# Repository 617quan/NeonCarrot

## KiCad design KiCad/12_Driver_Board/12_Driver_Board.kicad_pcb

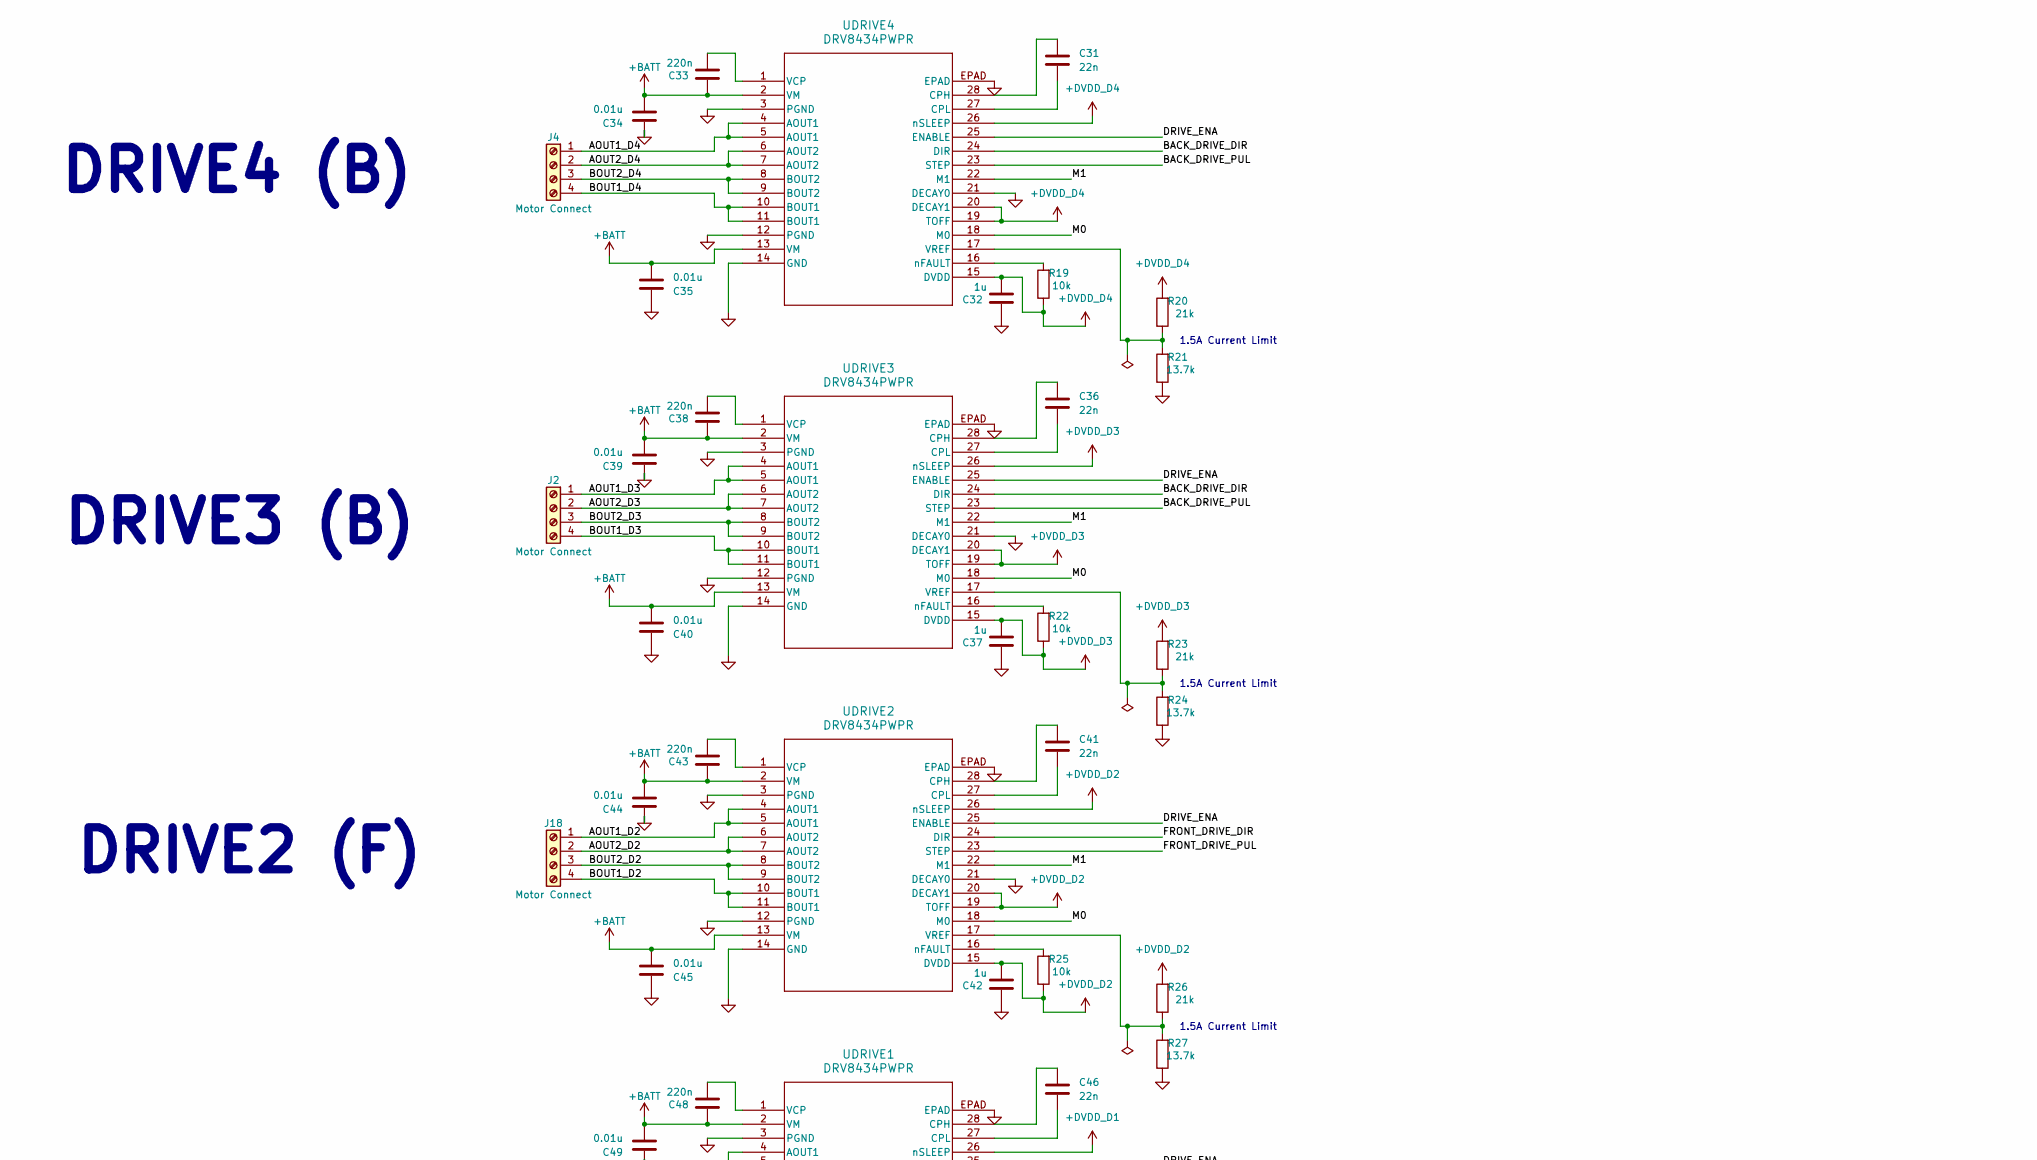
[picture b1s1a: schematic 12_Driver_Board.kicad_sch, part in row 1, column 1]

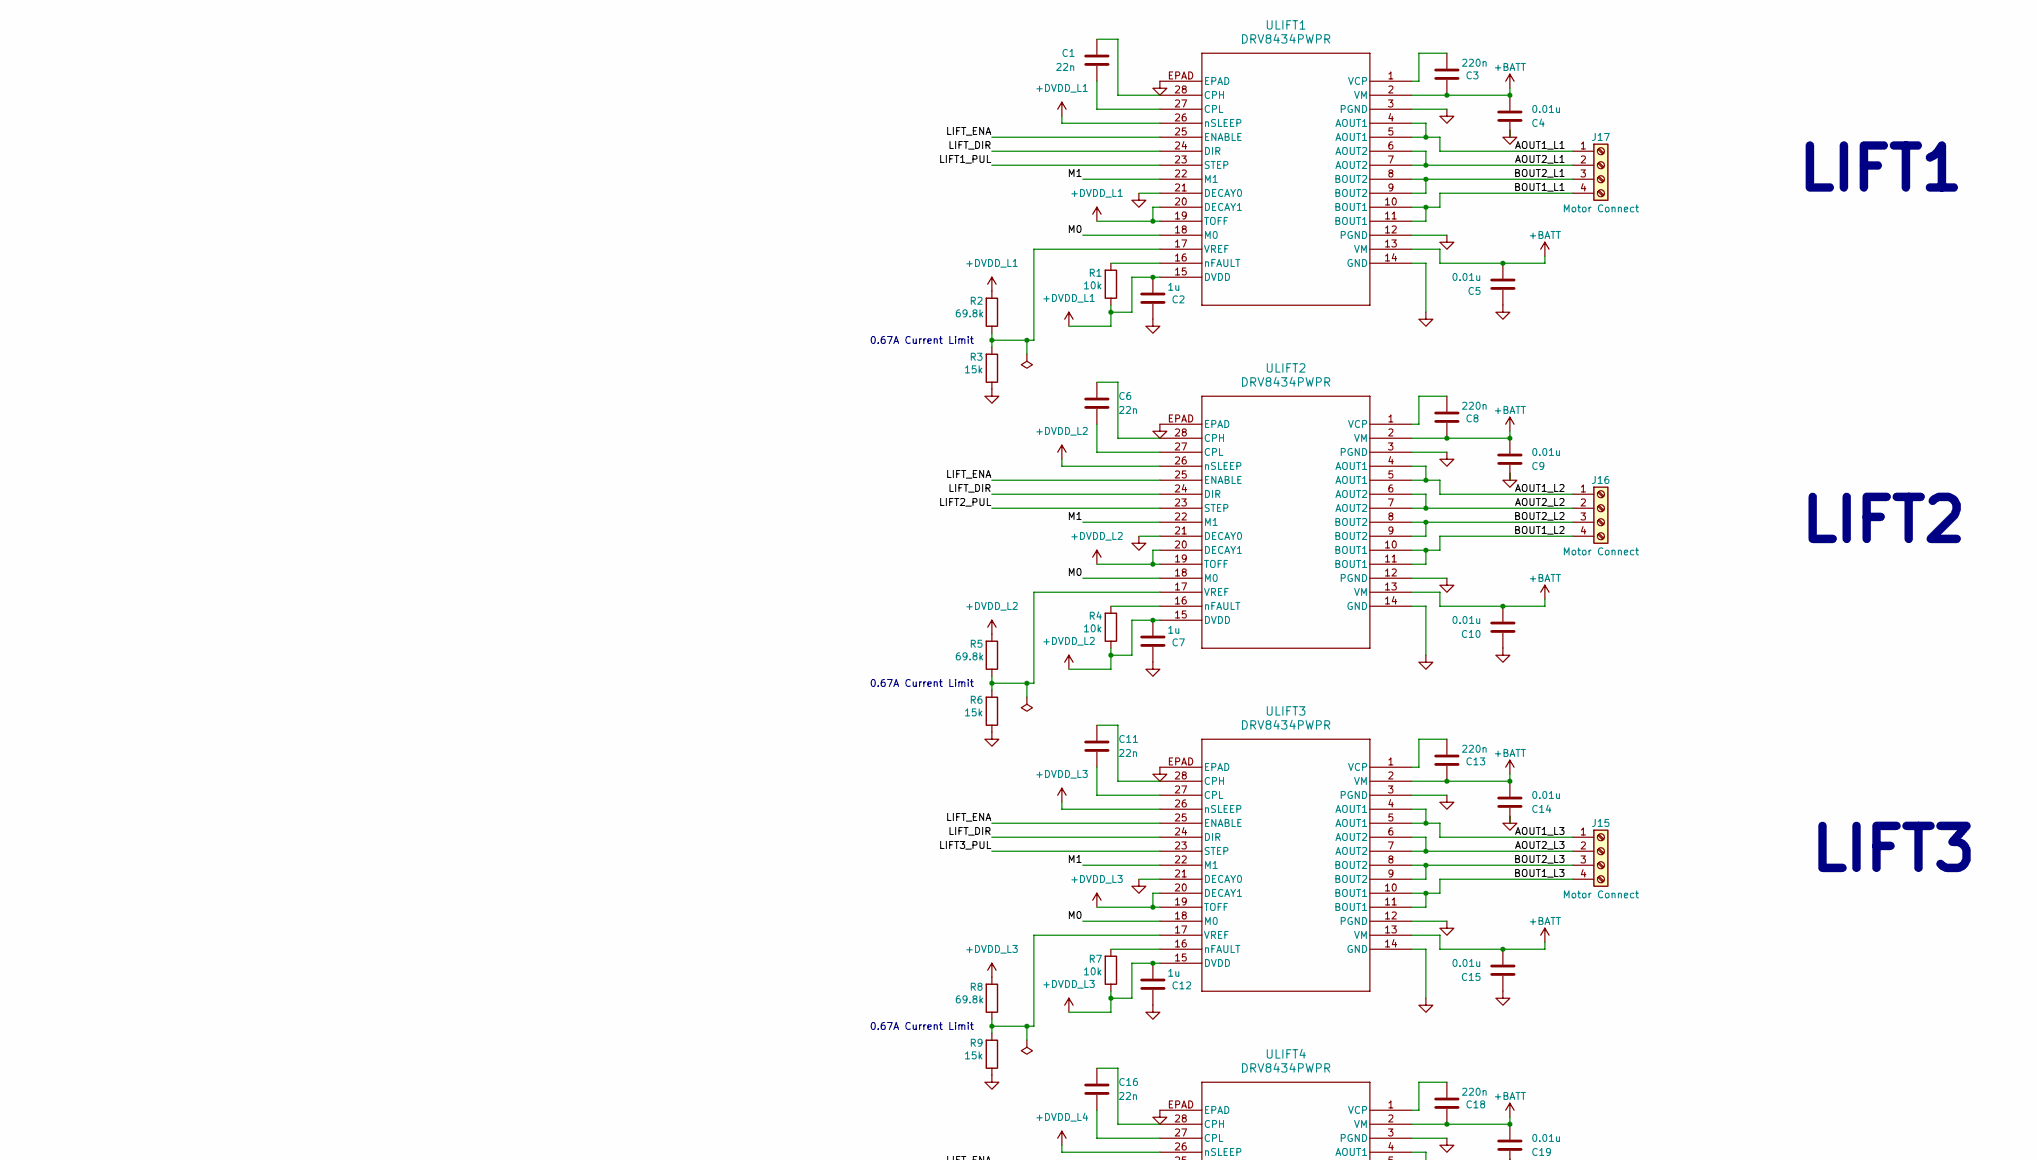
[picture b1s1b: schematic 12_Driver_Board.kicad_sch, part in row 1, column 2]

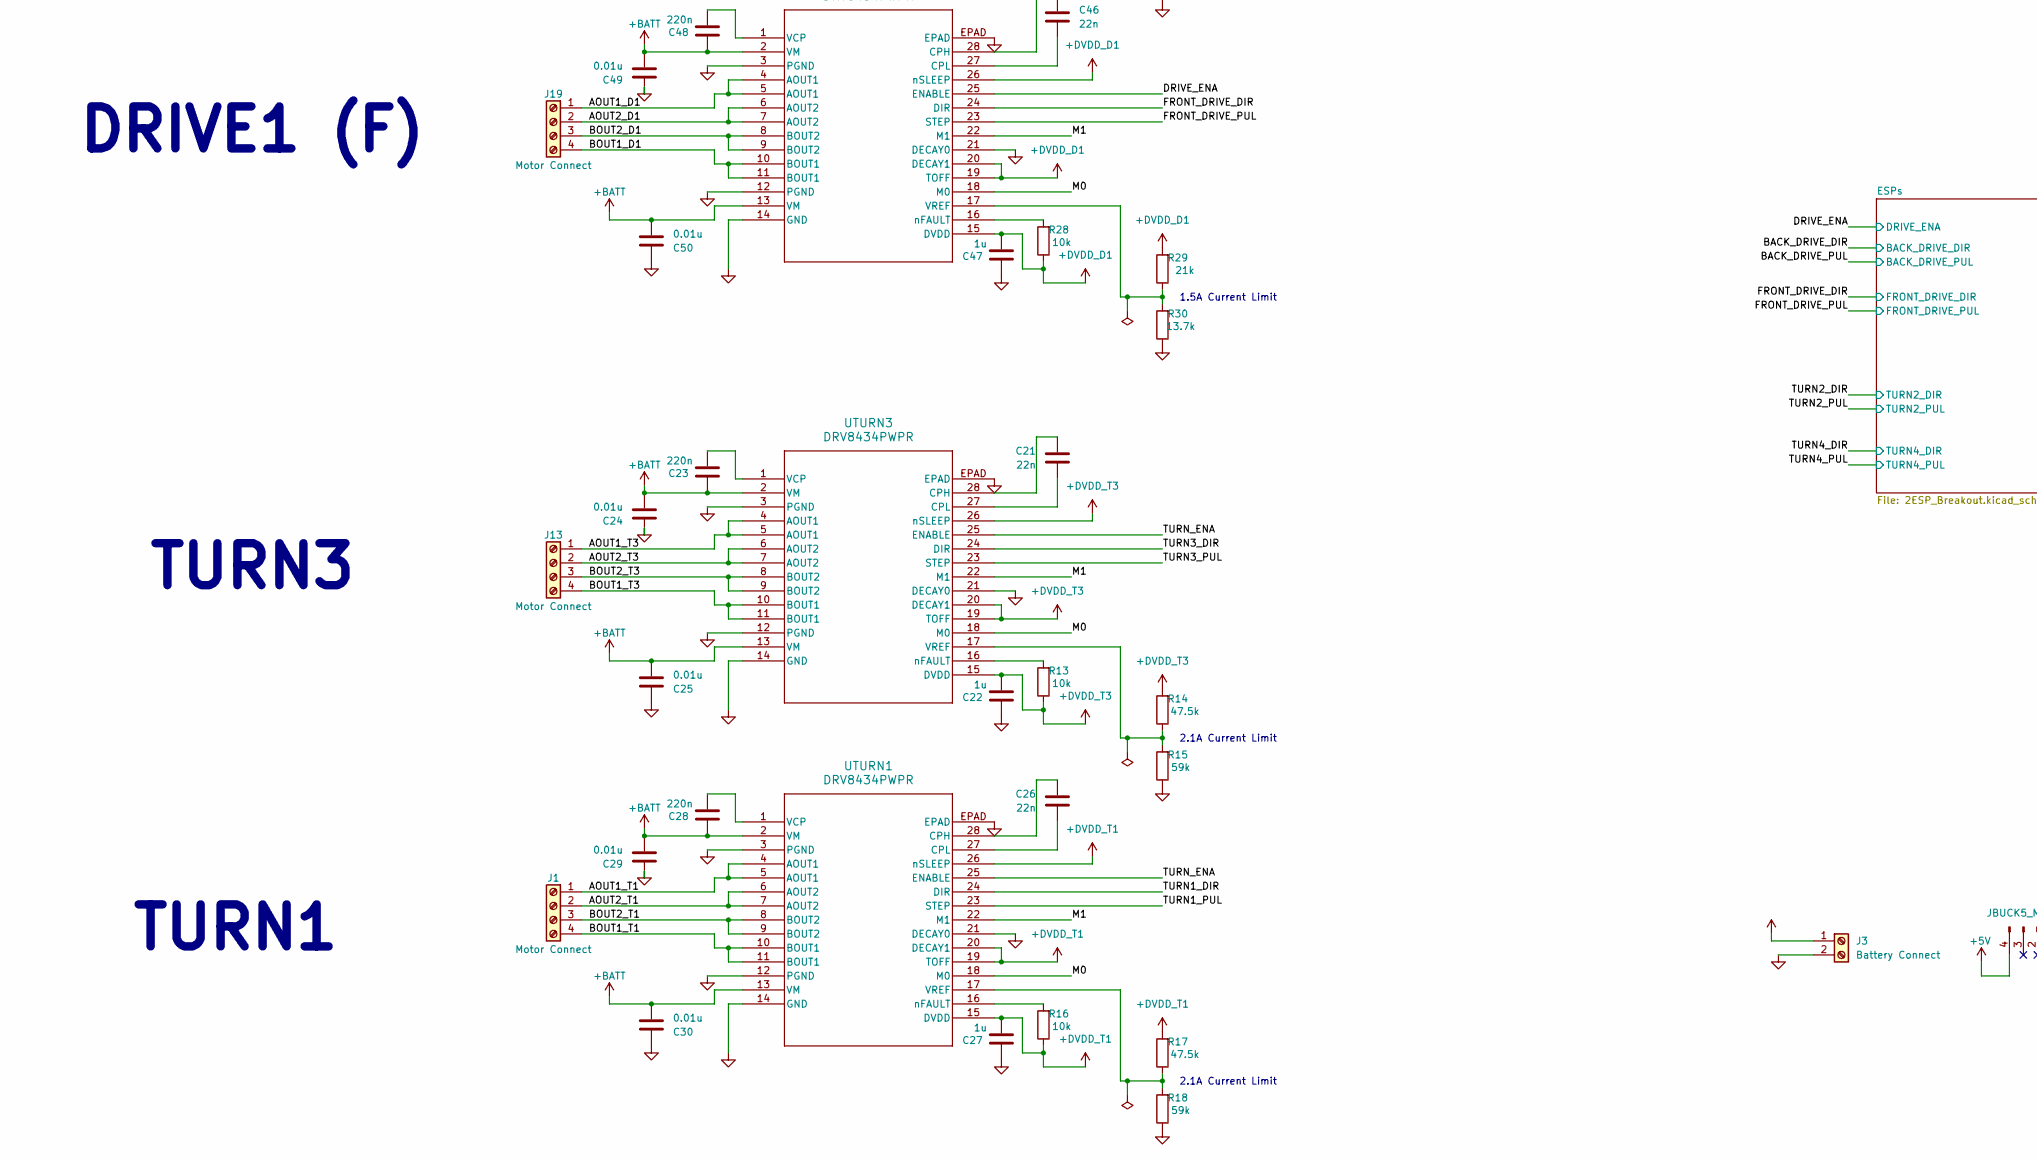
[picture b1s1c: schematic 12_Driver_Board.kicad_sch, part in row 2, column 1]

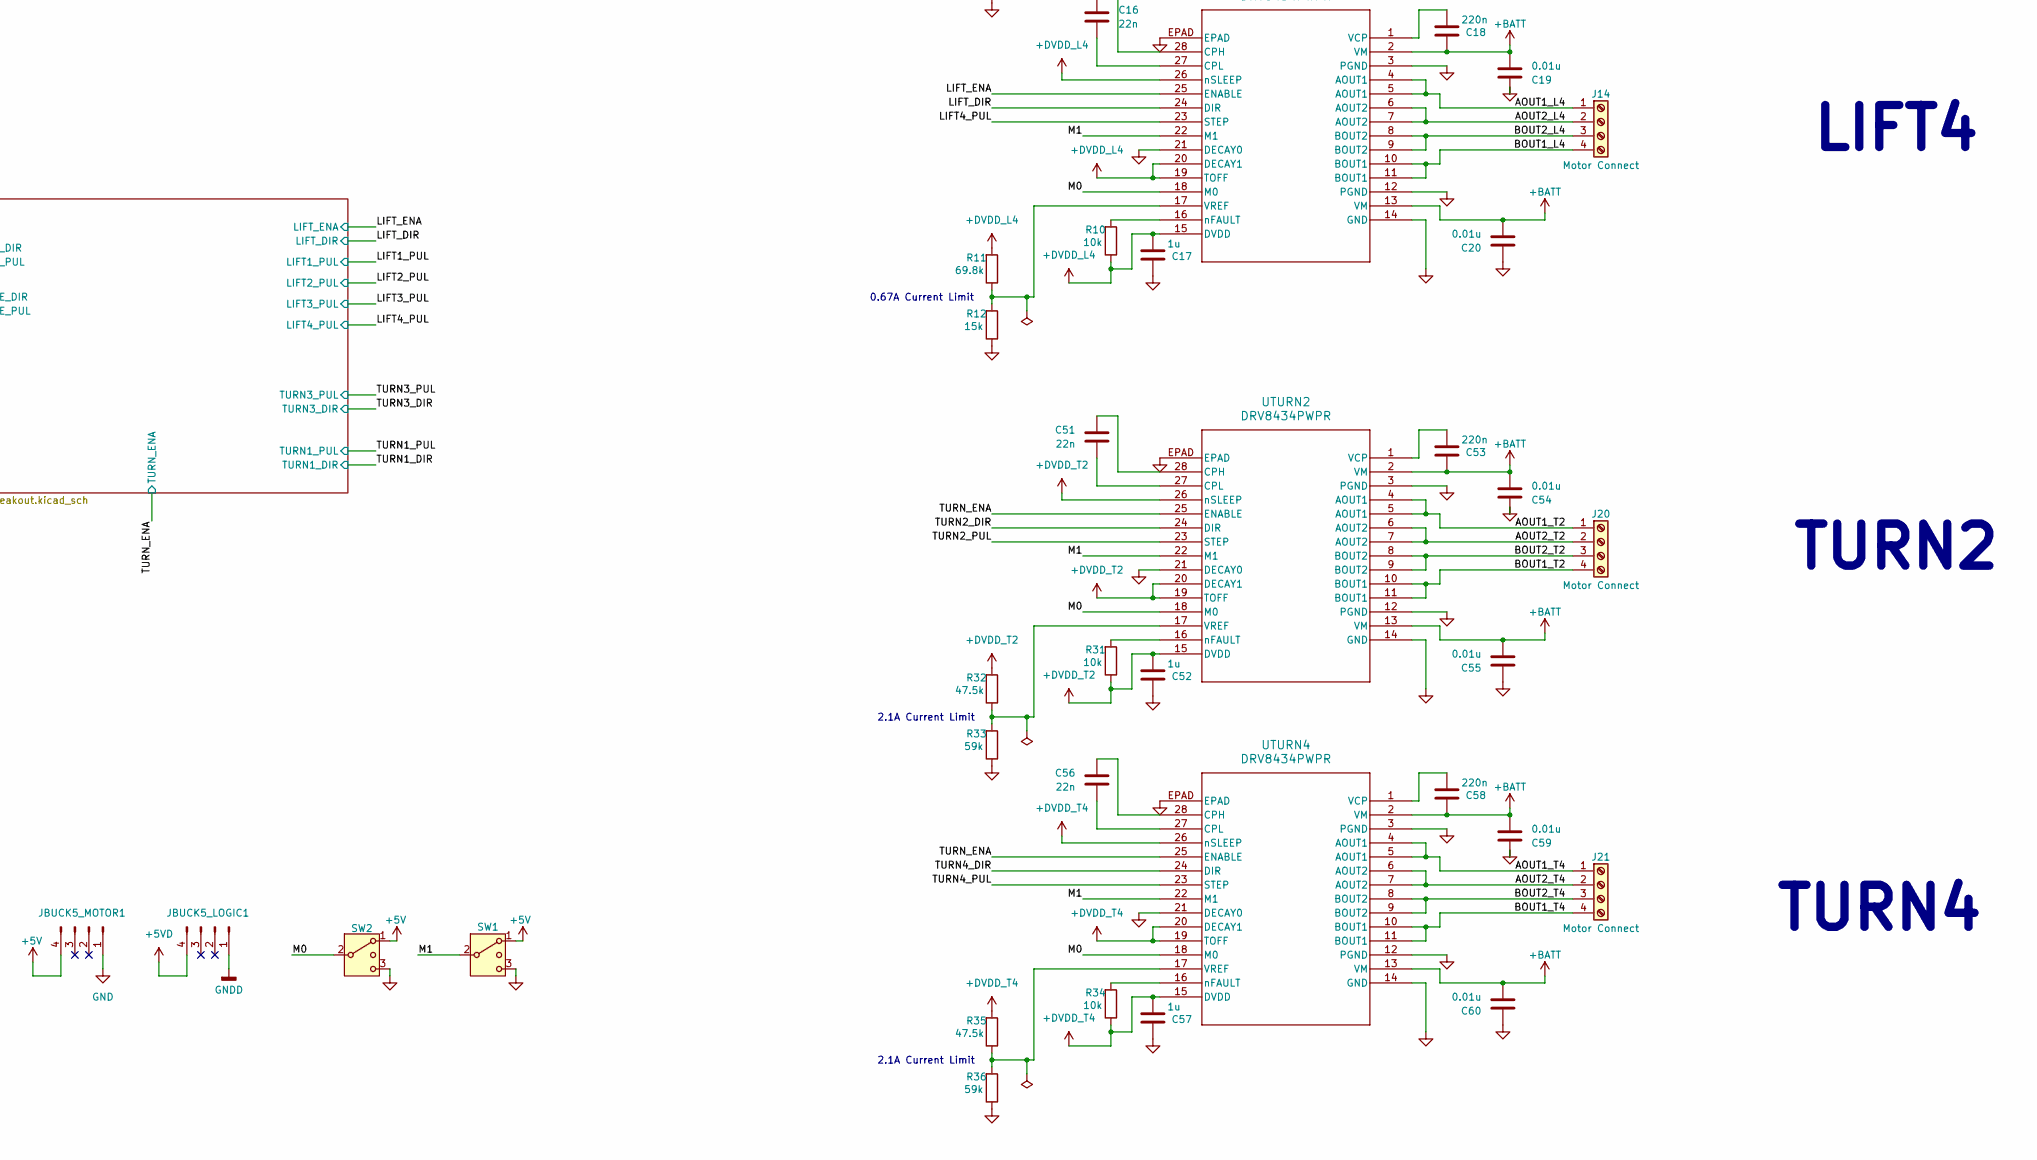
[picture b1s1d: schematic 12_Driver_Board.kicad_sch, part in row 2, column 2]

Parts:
C1, C6, C11, C16, C21, C26, C31, C36, C41, C46, C51, C56: 22n; C_0603_1608Metric
C2, C7, C12, C17, C22, C27, C32, C37, C42, C47, C52, C57: 1u; C_0603_1608Metric
C3, C8, C13, C18, C23, C28, C33, C38, C43, C48, C53, C58: 220n; C_0603_1608Metric
C4, C5, C9, C10, C14, C15, C19, C20, C24, C25, C29, C30, C34, C35, C39, C40, C44, C45, C49, C50, C54, C55, C59, C60: 0.01u; C_0603_1608Metric
J1, J2, J4, J13, J14, J15, J16, J17, J18, J19, J20, J21: Motor Connect; PhoenixContact_MSTBA_2,5_4-G-5,08_1x04_P5.08mm_Horizontal
J3: Battery Connect; PhoenixContact_MSTBA_2,5_2-G-5,08_1x02_P5.08mm_Horizontal
JBUCK5_LOGIC1, JBUCK5_MOTOR1: Conn_01x04_Pin
R1, R4, R7, R10, R13, R16, R19, R22, R25, R28, R31, R34: 10k; R_0603_1608Metric
R2, R5, R8, R11: 69.8k; R_0603_1608Metric
R3, R6, R9, R12: 15k; R_0603_1608Metric
R14, R17, R32, R35: 47.5k; R_0603_1608Metric
R15, R18, R33, R36: 59k; R_0603_1608Metric
R20, R23, R26, R29: 21k; R_0603_1608Metric
R21, R24, R27, R30: 13.7k; R_0603_1608Metric
SW1, SW2: SW_SPDT_MSM; SW_Slide_SPDT_Straight_CK_OS102011MS2Q
UDRIVE1, UDRIVE2, UDRIVE3, UDRIVE4: DRV8434PWPR; TSSOP_34PWPR_TEX
ULIFT1, ULIFT2, ULIFT3, ULIFT4: DRV8434PWPR; TSSOP_34PWPR_TEX
UTURN1, UTURN2, UTURN3, UTURN4: DRV8434PWPR; TSSOP_34PWPR_TEX

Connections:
+5V: JBUCK5_MOTOR1.4, SW1.1, SW2.1; also elsewhere on the board
+BATT: C3.2, C4.1, C5.1, C8.2, C9.1, C10.1, C13.2, C14.1, C15.1, C18.2, C19.1, C20.1, C23.2, C24.1, C25.1, C28.2, C29.1, C30.1, C33.2, C34.1, C35.1, C38.2, C39.1, C40.1, C43.2, C44.1, C45.1, C48.2, C49.1, C50.1, C53.2, C54.1, C55.1, C58.2, C59.1, C60.1, J3.1, UDRIVE1.2 (VM), UDRIVE1.13 (VM), UDRIVE2.2 (VM), UDRIVE2.13 (VM), UDRIVE3.2 (VM), UDRIVE3.13 (VM), UDRIVE4.2 (VM), UDRIVE4.13 (VM), ULIFT1.2 (VM), ULIFT1.13 (VM), ULIFT2.2 (VM), ULIFT2.13 (VM), ULIFT3.2 (VM), ULIFT3.13 (VM), ULIFT4.2 (VM), ULIFT4.13 (VM), UTURN1.2 (VM), UTURN1.13 (VM), UTURN2.2 (VM), UTURN2.13 (VM), UTURN3.2 (VM), UTURN3.13 (VM), UTURN4.2 (VM), UTURN4.13 (VM)
+DVDD_D1: C47.1, R28.1, R29.2, UDRIVE1.15 (DVDD), UDRIVE1.19 (TOFF), UDRIVE1.20 (DECAY1), UDRIVE1.26 (nSLEEP)
+DVDD_D2: C42.1, R25.1, R26.2, UDRIVE2.15 (DVDD), UDRIVE2.19 (TOFF), UDRIVE2.20 (DECAY1), UDRIVE2.26 (nSLEEP)
+DVDD_D3: C37.1, R22.1, R23.2, UDRIVE3.15 (DVDD), UDRIVE3.19 (TOFF), UDRIVE3.20 (DECAY1), UDRIVE3.26 (nSLEEP)
+DVDD_D4: C32.1, R19.1, R20.2, UDRIVE4.15 (DVDD), UDRIVE4.19 (TOFF), UDRIVE4.20 (DECAY1), UDRIVE4.26 (nSLEEP)
+DVDD_L1: C2.1, R1.1, R2.2, ULIFT1.15 (DVDD), ULIFT1.19 (TOFF), ULIFT1.20 (DECAY1), ULIFT1.26 (nSLEEP)
+DVDD_L2: C7.1, R4.1, R5.2, ULIFT2.15 (DVDD), ULIFT2.19 (TOFF), ULIFT2.20 (DECAY1), ULIFT2.26 (nSLEEP)
+DVDD_L3: C12.1, R7.1, R8.2, ULIFT3.15 (DVDD), ULIFT3.19 (TOFF), ULIFT3.20 (DECAY1), ULIFT3.26 (nSLEEP)
+DVDD_L4: C17.1, R10.1, R11.2, ULIFT4.15 (DVDD), ULIFT4.19 (TOFF), ULIFT4.20 (DECAY1), ULIFT4.26 (nSLEEP)
+DVDD_T1: C27.1, R16.1, R17.2, UTURN1.15 (DVDD), UTURN1.19 (TOFF), UTURN1.20 (DECAY1), UTURN1.26 (nSLEEP)
+DVDD_T2: C52.1, R31.1, R32.2, UTURN2.15 (DVDD), UTURN2.19 (TOFF), UTURN2.20 (DECAY1), UTURN2.26 (nSLEEP)
+DVDD_T3: C22.1, R13.1, R14.2, UTURN3.15 (DVDD), UTURN3.19 (TOFF), UTURN3.20 (DECAY1), UTURN3.26 (nSLEEP)
+DVDD_T4: C57.1, R34.1, R35.2, UTURN4.15 (DVDD), UTURN4.19 (TOFF), UTURN4.20 (DECAY1), UTURN4.26 (nSLEEP)
/AOUT1_D1: J19.1, UDRIVE1.4 (AOUT1), UDRIVE1.5 (AOUT1)
/AOUT1_D2: J18.1, UDRIVE2.4 (AOUT1), UDRIVE2.5 (AOUT1)
/AOUT1_D3: J2.1, UDRIVE3.4 (AOUT1), UDRIVE3.5 (AOUT1)
/AOUT1_D4: J4.1, UDRIVE4.4 (AOUT1), UDRIVE4.5 (AOUT1)
/AOUT1_L1: J17.1, ULIFT1.4 (AOUT1), ULIFT1.5 (AOUT1)
/AOUT1_L2: J16.1, ULIFT2.4 (AOUT1), ULIFT2.5 (AOUT1)
/AOUT1_L3: J15.1, ULIFT3.4 (AOUT1), ULIFT3.5 (AOUT1)
/AOUT1_L4: J14.1, ULIFT4.4 (AOUT1), ULIFT4.5 (AOUT1)
/AOUT1_T1: J1.1, UTURN1.4 (AOUT1), UTURN1.5 (AOUT1)
/AOUT1_T2: J20.1, UTURN2.4 (AOUT1), UTURN2.5 (AOUT1)
/AOUT1_T3: J13.1, UTURN3.4 (AOUT1), UTURN3.5 (AOUT1)
/AOUT1_T4: J21.1, UTURN4.4 (AOUT1), UTURN4.5 (AOUT1)
/AOUT2_D1: J19.2, UDRIVE1.6 (AOUT2), UDRIVE1.7 (AOUT2)
/AOUT2_D2: J18.2, UDRIVE2.6 (AOUT2), UDRIVE2.7 (AOUT2)
/AOUT2_D3: J2.2, UDRIVE3.6 (AOUT2), UDRIVE3.7 (AOUT2)
/AOUT2_D4: J4.2, UDRIVE4.6 (AOUT2), UDRIVE4.7 (AOUT2)
/AOUT2_L1: J17.2, ULIFT1.6 (AOUT2), ULIFT1.7 (AOUT2)
/AOUT2_L2: J16.2, ULIFT2.6 (AOUT2), ULIFT2.7 (AOUT2)
/AOUT2_L3: J15.2, ULIFT3.6 (AOUT2), ULIFT3.7 (AOUT2)
/AOUT2_L4: J14.2, ULIFT4.6 (AOUT2), ULIFT4.7 (AOUT2)
/AOUT2_T1: J1.2, UTURN1.6 (AOUT2), UTURN1.7 (AOUT2)
/AOUT2_T2: J20.2, UTURN2.6 (AOUT2), UTURN2.7 (AOUT2)
/AOUT2_T3: J13.2, UTURN3.6 (AOUT2), UTURN3.7 (AOUT2)
/AOUT2_T4: J21.2, UTURN4.6 (AOUT2), UTURN4.7 (AOUT2)
/BACK_DRIVE_DIR: UDRIVE3.24 (DIR), UDRIVE4.24 (DIR); also elsewhere on the board
/BACK_DRIVE_PUL: UDRIVE3.23 (STEP), UDRIVE4.23 (STEP); also elsewhere on the board
/BOUT1_D1: J19.4, UDRIVE1.10 (BOUT1), UDRIVE1.11 (BOUT1)
/BOUT1_D2: J18.4, UDRIVE2.10 (BOUT1), UDRIVE2.11 (BOUT1)
/BOUT1_D3: J2.4, UDRIVE3.10 (BOUT1), UDRIVE3.11 (BOUT1)
/BOUT1_D4: J4.4, UDRIVE4.10 (BOUT1), UDRIVE4.11 (BOUT1)
/BOUT1_L1: J17.4, ULIFT1.10 (BOUT1), ULIFT1.11 (BOUT1)
/BOUT1_L2: J16.4, ULIFT2.10 (BOUT1), ULIFT2.11 (BOUT1)
/BOUT1_L3: J15.4, ULIFT3.10 (BOUT1), ULIFT3.11 (BOUT1)
/BOUT1_L4: J14.4, ULIFT4.10 (BOUT1), ULIFT4.11 (BOUT1)
/BOUT1_T1: J1.4, UTURN1.10 (BOUT1), UTURN1.11 (BOUT1)
/BOUT1_T2: J20.4, UTURN2.10 (BOUT1), UTURN2.11 (BOUT1)
/BOUT1_T3: J13.4, UTURN3.10 (BOUT1), UTURN3.11 (BOUT1)
/BOUT1_T4: J21.4, UTURN4.10 (BOUT1), UTURN4.11 (BOUT1)
/BOUT2_D1: J19.3, UDRIVE1.8 (BOUT2), UDRIVE1.9 (BOUT2)
/BOUT2_D2: J18.3, UDRIVE2.8 (BOUT2), UDRIVE2.9 (BOUT2)
/BOUT2_D3: J2.3, UDRIVE3.8 (BOUT2), UDRIVE3.9 (BOUT2)
/BOUT2_D4: J4.3, UDRIVE4.8 (BOUT2), UDRIVE4.9 (BOUT2)
/BOUT2_L1: J17.3, ULIFT1.8 (BOUT2), ULIFT1.9 (BOUT2)
/BOUT2_L2: J16.3, ULIFT2.8 (BOUT2), ULIFT2.9 (BOUT2)
/BOUT2_L3: J15.3, ULIFT3.8 (BOUT2), ULIFT3.9 (BOUT2)
/BOUT2_L4: J14.3, ULIFT4.8 (BOUT2), ULIFT4.9 (BOUT2)
/BOUT2_T1: J1.3, UTURN1.8 (BOUT2), UTURN1.9 (BOUT2)
/BOUT2_T2: J20.3, UTURN2.8 (BOUT2), UTURN2.9 (BOUT2)
/BOUT2_T3: J13.3, UTURN3.8 (BOUT2), UTURN3.9 (BOUT2)
/BOUT2_T4: J21.3, UTURN4.8 (BOUT2), UTURN4.9 (BOUT2)
/DRIVE_ENA: UDRIVE1.25 (ENABLE), UDRIVE2.25 (ENABLE), UDRIVE3.25 (ENABLE), UDRIVE4.25 (ENABLE); also elsewhere on the board
/FRONT_DRIVE_DIR: UDRIVE1.24 (DIR), UDRIVE2.24 (DIR); also elsewhere on the board
/FRONT_DRIVE_PUL: UDRIVE1.23 (STEP), UDRIVE2.23 (STEP); also elsewhere on the board
/LIFT1_PUL: ULIFT1.23 (STEP); also elsewhere on the board
/LIFT2_PUL: ULIFT2.23 (STEP); also elsewhere on the board
/LIFT3_PUL: ULIFT3.23 (STEP); also elsewhere on the board
/LIFT4_PUL: ULIFT4.23 (STEP); also elsewhere on the board
/LIFT_DIR: ULIFT1.24 (DIR), ULIFT2.24 (DIR), ULIFT3.24 (DIR), ULIFT4.24 (DIR); also elsewhere on the board
/LIFT_ENA: ULIFT1.25 (ENABLE), ULIFT2.25 (ENABLE), ULIFT3.25 (ENABLE), ULIFT4.25 (ENABLE); also elsewhere on the board
/M0: SW2.2 (3), UDRIVE1.18 (M0), UDRIVE2.18 (M0), UDRIVE3.18 (M0), UDRIVE4.18 (M0), ULIFT1.18 (M0), ULIFT2.18 (M0), ULIFT3.18 (M0), ULIFT4.18 (M0), UTURN1.18 (M0), UTURN2.18 (M0), UTURN3.18 (M0), UTURN4.18 (M0)
/M1: SW1.2 (3), UDRIVE1.22 (M1), UDRIVE2.22 (M1), UDRIVE3.22 (M1), UDRIVE4.22 (M1), ULIFT1.22 (M1), ULIFT2.22 (M1), ULIFT3.22 (M1), ULIFT4.22 (M1), UTURN1.22 (M1), UTURN2.22 (M1), UTURN3.22 (M1), UTURN4.22 (M1)
/TURN1_DIR: UTURN1.24 (DIR); also elsewhere on the board
/TURN1_PUL: UTURN1.23 (STEP); also elsewhere on the board
/TURN2_DIR: UTURN2.24 (DIR); also elsewhere on the board
/TURN2_PUL: UTURN2.23 (STEP); also elsewhere on the board
/TURN3_DIR: UTURN3.24 (DIR); also elsewhere on the board
/TURN3_PUL: UTURN3.23 (STEP); also elsewhere on the board
/TURN4_DIR: UTURN4.24 (DIR); also elsewhere on the board
/TURN4_PUL: UTURN4.23 (STEP); also elsewhere on the board
/TURN_ENA: UTURN1.25 (ENABLE), UTURN2.25 (ENABLE), UTURN3.25 (ENABLE), UTURN4.25 (ENABLE); also elsewhere on the board
GND: C2.2, C4.2, C5.2, C7.2, C9.2, C10.2, C12.2, C14.2, C15.2, C17.2, C19.2, C20.2, C22.2, C24.2, C25.2, C27.2, C29.2, C30.2, C32.2, C34.2, C35.2, C37.2, C39.2, C40.2, C42.2, C44.2, C45.2, C47.2, C49.2, C50.2, C52.2, C54.2, C55.2, C57.2, C59.2, C60.2, J3.2, JBUCK5_MOTOR1.1, R3.1, R6.1, R9.1, R12.1, R15.1, R18.1, R21.1, R24.1, R27.1, R30.1, R33.1, R36.1, SW1.3 (4), SW2.3 (4), UDRIVE1.3 (PGND), UDRIVE1.12 (PGND), UDRIVE1.14 (GND), UDRIVE1.21 (DECAY0), UDRIVE1.EPAD, UDRIVE2.3 (PGND), UDRIVE2.12 (PGND), UDRIVE2.14 (GND), UDRIVE2.21 (DECAY0), UDRIVE2.EPAD, UDRIVE3.3 (PGND), UDRIVE3.12 (PGND), UDRIVE3.14 (GND), UDRIVE3.21 (DECAY0), UDRIVE3.EPAD, UDRIVE4.3 (PGND), UDRIVE4.12 (PGND), UDRIVE4.14 (GND), UDRIVE4.21 (DECAY0), UDRIVE4.EPAD, ULIFT1.3 (PGND), ULIFT1.12 (PGND), ULIFT1.14 (GND), ULIFT1.21 (DECAY0), ULIFT1.EPAD, ULIFT2.3 (PGND), ULIFT2.12 (PGND), ULIFT2.14 (GND), ULIFT2.21 (DECAY0), ULIFT2.EPAD, ULIFT3.3 (PGND), ULIFT3.12 (PGND), ULIFT3.14 (GND), ULIFT3.21 (DECAY0), ULIFT3.EPAD, ULIFT4.3 (PGND), ULIFT4.12 (PGND), ULIFT4.14 (GND), ULIFT4.21 (DECAY0), ULIFT4.EPAD, UTURN1.3 (PGND), UTURN1.12 (PGND), UTURN1.14 (GND), UTURN1.21 (DECAY0), UTURN1.EPAD, UTURN2.3 (PGND), UTURN2.12 (PGND), UTURN2.14 (GND), UTURN2.21 (DECAY0), UTURN2.EPAD, UTURN3.3 (PGND), UTURN3.12 (PGND), UTURN3.14 (GND), UTURN3.21 (DECAY0), UTURN3.EPAD, UTURN4.3 (PGND), UTURN4.12 (PGND), UTURN4.14 (GND), UTURN4.21 (DECAY0), UTURN4.EPAD; also elsewhere on the board
unnamed: C46.1, UDRIVE1.28 (CPH)
unnamed: C46.2, UDRIVE1.27 (CPL)
unnamed: C48.1, UDRIVE1.1 (VCP)
unnamed: R29.1, R30.2, UDRIVE1.17 (VREF)
unnamed: R28.2, UDRIVE1.16 (nFAULT)
unnamed: C41.1, UDRIVE2.28 (CPH)
unnamed: C41.2, UDRIVE2.27 (CPL)
unnamed: C43.1, UDRIVE2.1 (VCP)
unnamed: R26.1, R27.2, UDRIVE2.17 (VREF)
unnamed: R25.2, UDRIVE2.16 (nFAULT)
unnamed: C36.1, UDRIVE3.28 (CPH)
unnamed: C36.2, UDRIVE3.27 (CPL)
unnamed: C38.1, UDRIVE3.1 (VCP)
unnamed: R23.1, R24.2, UDRIVE3.17 (VREF)
unnamed: R22.2, UDRIVE3.16 (nFAULT)
unnamed: C31.1, UDRIVE4.28 (CPH)
unnamed: C31.2, UDRIVE4.27 (CPL)
unnamed: C33.1, UDRIVE4.1 (VCP)
unnamed: R20.1, R21.2, UDRIVE4.17 (VREF)
unnamed: R19.2, UDRIVE4.16 (nFAULT)
unnamed: C1.1, ULIFT1.28 (CPH)
unnamed: C1.2, ULIFT1.27 (CPL)
unnamed: C3.1, ULIFT1.1 (VCP)
unnamed: R2.1, R3.2, ULIFT1.17 (VREF)
unnamed: R1.2, ULIFT1.16 (nFAULT)
unnamed: C6.1, ULIFT2.28 (CPH)
unnamed: C6.2, ULIFT2.27 (CPL)
unnamed: C8.1, ULIFT2.1 (VCP)
unnamed: R5.1, R6.2, ULIFT2.17 (VREF)
unnamed: R4.2, ULIFT2.16 (nFAULT)
unnamed: C11.1, ULIFT3.28 (CPH)
unnamed: C11.2, ULIFT3.27 (CPL)
unnamed: C13.1, ULIFT3.1 (VCP)
unnamed: R8.1, R9.2, ULIFT3.17 (VREF)
unnamed: R7.2, ULIFT3.16 (nFAULT)
unnamed: C16.1, ULIFT4.28 (CPH)
unnamed: C16.2, ULIFT4.27 (CPL)
unnamed: C18.1, ULIFT4.1 (VCP)
unnamed: R11.1, R12.2, ULIFT4.17 (VREF)
unnamed: R10.2, ULIFT4.16 (nFAULT)
unnamed: C26.1, UTURN1.28 (CPH)
unnamed: C26.2, UTURN1.27 (CPL)
unnamed: C28.1, UTURN1.1 (VCP)
unnamed: R17.1, R18.2, UTURN1.17 (VREF)
unnamed: R16.2, UTURN1.16 (nFAULT)
unnamed: C51.1, UTURN2.28 (CPH)
unnamed: C51.2, UTURN2.27 (CPL)
unnamed: C53.1, UTURN2.1 (VCP)
unnamed: R32.1, R33.2, UTURN2.17 (VREF)
unnamed: R31.2, UTURN2.16 (nFAULT)
unnamed: C21.1, UTURN3.28 (CPH)
unnamed: C21.2, UTURN3.27 (CPL)
unnamed: C23.1, UTURN3.1 (VCP)
unnamed: R14.1, R15.2, UTURN3.17 (VREF)
unnamed: R13.2, UTURN3.16 (nFAULT)
unnamed: C56.1, UTURN4.28 (CPH)
unnamed: C56.2, UTURN4.27 (CPL)
unnamed: C58.1, UTURN4.1 (VCP)
unnamed: R35.1, R36.2, UTURN4.17 (VREF)
unnamed: R34.2, UTURN4.16 (nFAULT)

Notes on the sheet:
DRIVE3 (B)
0.67A Current Limit
TURN2
2.1A Current Limit
TURN4
LIFT4
DRIVE2 (F)
1.5A Current Limit
LIFT1
LIFT2
DRIVE4 (B)
TURN3
DRIVE1 (F)
TURN1
LIFT3
